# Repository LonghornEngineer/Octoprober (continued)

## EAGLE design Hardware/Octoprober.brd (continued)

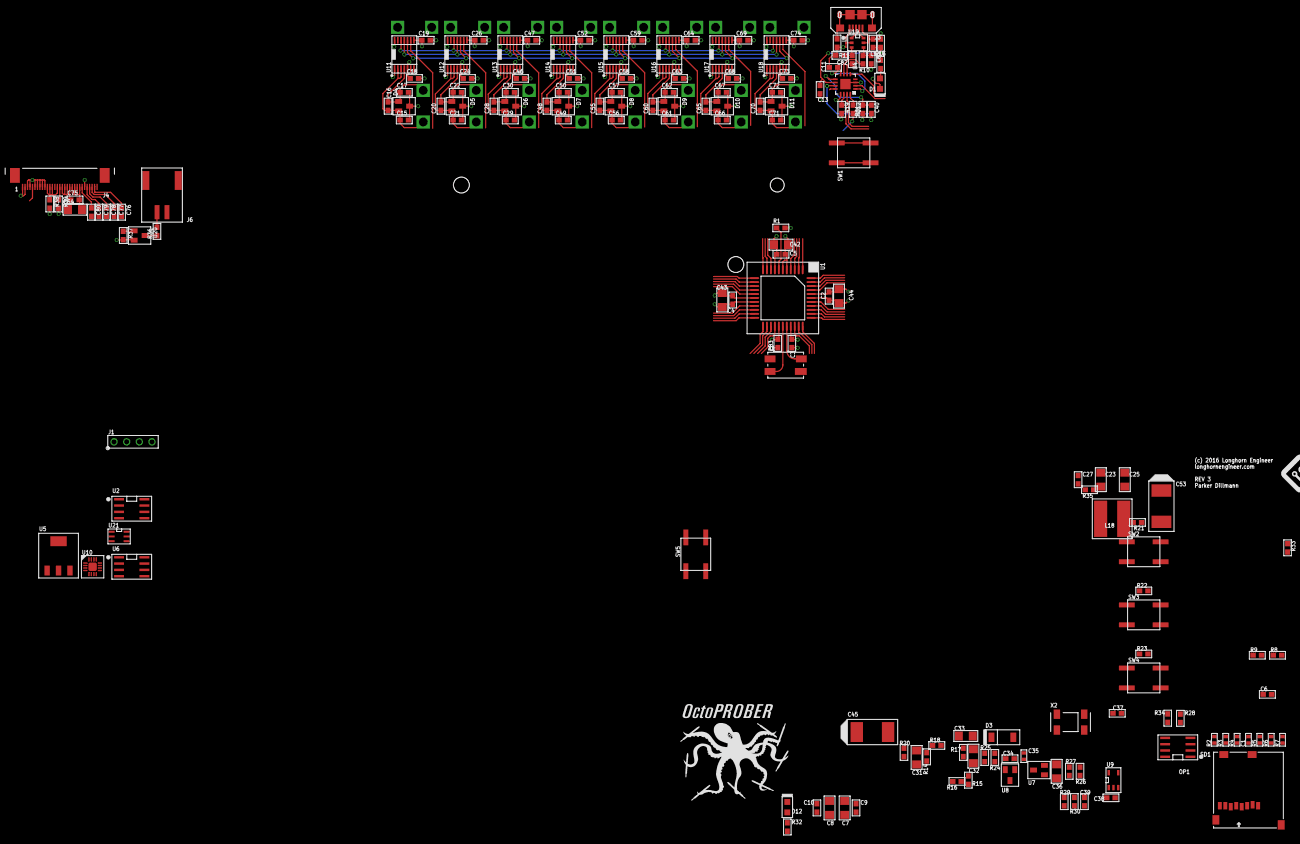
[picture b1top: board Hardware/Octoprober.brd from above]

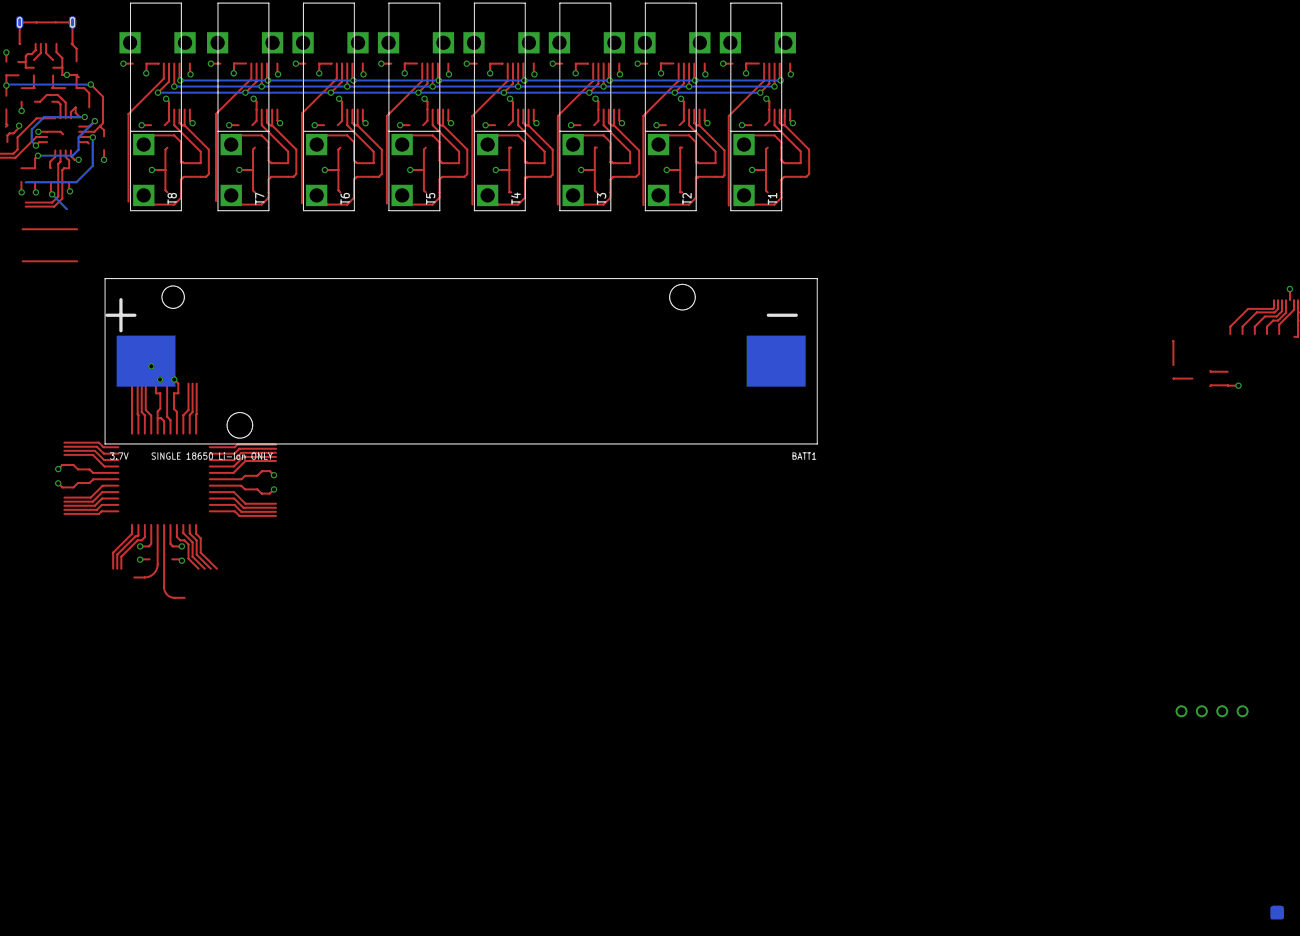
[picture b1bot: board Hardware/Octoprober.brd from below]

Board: 4 copper layers, 179 parts (9 on the bottom side), 104 nets.

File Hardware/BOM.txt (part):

"Part";"Value";"Device";"Package";"Description";"DNAME";"REVNUM";
"BATT1";"MIKROE-1120";"PH_1X02HEADER_PTH";"HEADER_01X02_PTH";"2 pin connectors";"";"";
"C1";"0.1uF";"CAPACITOR_NON_POLAR0402";"0402";"Capacitor Non Polarized";"";"";
"C2";"0.1uF";"CAPACITOR_NON_POLAR0402";"0402";"Capacitor Non Polarized";"";"";
"C3";"0.1uF";"CAPACITOR_NON_POLAR0402";"0402";"Capacitor Non Polarized";"";"";
"C4";"0.1uF";"CAPACITOR_NON_POLAR0402";"0402";"Capacitor Non Polarized";"";"";
"C5";"0.1uF";"CAPACITOR_NON_POLAR0402";"0402";"Capacitor Non Polarized";"";"";
"C6";"0.1uF";"CAPACITOR_NON_POLAR0402";"0402";"Capacitor Non Polarized";"";"";
"C7";"10uF";"CAPACITOR_NON_POLAR1206";"1206";"Capacitor Non Polarized";"";"";
"C8";"10uF";"CAPACITOR_NON_POLAR1206";"1206";"Capacitor Non Polarized";"";"";
"C9";"0.1uF";"CAPACITOR_NON_POLAR0402";"0402";"Capacitor Non Polarized";"";"";
"C10";"0.1uF";"CAPACITOR_NON_POLAR0402";"0402";"Capacitor Non Polarized";"";"";
"C11";"0.1uF";"CAPACITOR_NON_POLAR0402";"0402";"Capacitor Non Polarized";"";"";
"C12";"0.1uF";"CAPACITOR_NON_POLAR0402";"0402";"Capacitor Non Polarized";"";"";
"C13";"0.1uF";"CAPACITOR_NON_POLAR0402";"0402";"Capacitor Non Polarized";"";"";
"C14";"0.1uF";"CAPACITOR_NON_POLAR0402";"0402";"Capacitor Non Polarized";"";"";
"C15";"0.1uF";"CAPACITOR_NON_POLAR0402";"0402";"Capacitor Non Polarized";"";"";
"C16";"0.01uF";"CAPACITOR_NON_POLAR0402";"0402";"Capacitor Non Polarized";"";"";
"C17";"10uF";"CAPACITOR_NON_POLAR0402";"0402";"Capacitor Non Polarized";"";"";
"C18";"0.01uF";"CAPACITOR_NON_POLAR0402";"0402";"Capacitor Non Polarized";"";"";
"C19";"10uF";"CAPACITOR_NON_POLAR0402";"0402";"Capacitor Non Polarized";"";"";
"C20";"0.01uF";"CAPACITOR_NON_POLAR0402";"0402";"Capacitor Non Polarized";"";"";
"C21";"0.1uF";"CAPACITOR_NON_POLAR0402";"0402";"Capacitor Non Polarized";"";"";
"C22";"0.01uF";"CAPACITOR_NON_POLAR0402";"0402";"Capacitor Non Polarized";"";"";
"C23";"10uF";"CAPACITOR_NON_POLAR0402";"0402";"Capacitor Non Polarized";"";"";
"C24";"0.01uF";"CAPACITOR_NON_POLAR0402";"0402";"Capacitor Non Polarized";"";"";
"C25";"10uF";"CAPACITOR_NON_POLAR0402";"0402";"Capacitor Non Polarized";"";"";
"C26";"0.01uF";"CAPACITOR_NON_POLAR0402";"0402";"Capacitor Non Polarized";"";"";
"C27";"1uF";"CAPACITOR_NON_POLAR0402";"0402";"Capacitor Non Polarized";"";"";
"C28";"0.01uF";"CAPACITOR_NON_POLAR0402";"0402";"Capacitor Non Polarized";"";"";
"C29";"0.1uF";"CAPACITOR_NON_POLAR0402";"0402";"Capacitor Non Polarized";"";"";
"C30";"0.01uF";"CAPACITOR_NON_POLAR0402";"0402";"Capacitor Non Polarized";"";"";
"C31";"10uF";"CAPACITOR_NON_POLAR1206";"1206";"Capacitor Non Polarized";"";"";
"C32";"10uF";"CAPACITOR_NON_POLAR1206";"1206";"Capacitor Non Polarized";"";"";
"C33";"10uF";"CAPACITOR_NON_POLAR1206";"1206";"Capacitor Non Polarized";"";"";
"C34";"0.1uF";"CAPACITOR_NON_POLAR0402";"0402";"Capacitor Non Polarized";"";"";
"C35";"0.1uF";"CAPACITOR_NON_POLAR0402";"0402";"Capacitor Non Polarized";"";"";
"C36";"10uF";"CAPACITOR_NON_POLAR1206";"1206";"Capacitor Non Polarized";"";"";
"C37";"0.1uF";"CAPACITOR_NON_POLAR0402";"0402";"Capacitor Non Polarized";"";"";
"C38";"0.1uF";"CAPACITOR_NON_POLAR0402";"0402";"Capacitor Non Polarized";"";"";
"C39";"0.1uF";"CAPACITOR_NON_POLAR0402";"0402";"Capacitor Non Polarized";"";"";
"C40";"0.1uF";"CAPACITOR_NON_POLAR0402";"0402";"Capacitor Non Polarized";"";"";
"C41";"10uF";"CAPACITOR_NON_POLAR0402";"0402";"Capacitor Non Polarized";"";"";
"C42";"10uF";"CAPACITOR_NON_POLAR0402";"0402";"Capacitor Non Polarized";"";"";
"C43";"10uF";"CAPACITOR_NON_POLAR0402";"0402";"Capacitor Non Polarized";"";"";
"C44";"10uF";"CAPACITOR_NON_POLAR0402";"0402";"Capacitor Non Polarized";"";"";
"C45";"470uF";"CAPACITOR_POLARIZEDCASE_D";"CASE_D";"Polarized capacitors";"";"";
"C46";"0.1uF";"CAPACITOR_NON_POLAR0402";"0402";"Capacitor Non Polarized";"";"";
"C47";"0.1uF";"CAPACITOR_NON_POLAR0402";"0402";"Capacitor Non Polarized";"";"";
"C48";"0.1uF";"CAPACITOR_NON_POLAR0402";"0402";"Capacitor Non Polarized";"";"";
"C49";"0.1uF";"CAPACITOR_NON_POLAR0402";"0402";"Capacitor Non Polarized";"";"";
"C50";"0.1uF";"CAPACITOR_NON_POLAR0402";"0402";"Capacitor Non Polarized";"";"";
"C51";"0.1uF";"CAPACITOR_NON_POLAR0402";"0402";"Capacitor Non Polarized";"";"";
"C52";"0.1uF";"CAPACITOR_NON_POLAR0402";"0402";"Capacitor Non Polarized";"";"";
"C53";"470uF";"CAPACITOR_POLARIZEDCASE_D";"CASE_D";"Polarized capacitors";"";"";
"C54";"1uF";"CAPACITOR_NON_POLAR0402";"0402";"Capacitor Non Polarized";"";"";
"D1";"598-8070-107F";"LED_SINGLE0402";"LED_0402";"";"";"";
"D2";"598-8070-107F";"LED_SINGLE0402";"LED_0402";"";"";"";
"D3";"PMEG6030EP,115";"DIODESOD-128";"SOD-128";"Diode - Single";"";"";
"D4";"NUP2105LT1G";"TVS_DIODE_DUALSOT-23";"SOT-23";"";"";"";
"D5";"NUP2105LT1G";"TVS_DIODE_DUALSOT-23";"SOT-23";"";"";"";
"D6";"NUP2105LT1G";"TVS_DIODE_DUALSOT-23";"SOT-23";"";"";"";
"D7";"NUP2105LT1G";"TVS_DIODE_DUALSOT-23";"SOT-23";"";"";"";
"D8";"NUP2105LT1G";"TVS_DIODE_DUALSOT-23";"SOT-23";"";"";"";
"D9";"NUP2105LT1G";"TVS_DIODE_DUALSOT-23";"SOT-23";"";"";"";
"D10";"NUP2105LT1G";"TVS_DIODE_DUALSOT-23";"SOT-23";"";"";"";
"D11";"NUP2105LT1G";"TVS_DIODE_DUALSOT-23";"SOT-23";"";"";"";
"D12";"598-8070-107F";"LED_SINGLE0402";"LED_0402";"";"";"";
"FU";"";"PH_1X09PTH";"HEADER_01X09_PTH";"";"";"";
"J1";"10118193-0001LF";"USB10118193-0001LF";"10118193-0001LF";"";"";"";
"J2";"";"PH_1X04HEADER_PTH";"HEADER_01X04_PTH";"4 Pin Connectors";"";"";
"L1";"MI0603K300R-10";"RESISTOR0603";"0603";"Resistors";"";"";
"L2";"BK1005HM471-T";"INDUCTOR0402";"0402";"Inductors";"";"";
"L3";"BK1005HM471-T";"INDUCTOR0402";"0402";"Inductors";"";"";
"L4";"BK1005HM471-T";"INDUCTOR0402";"0402";"Inductors";"";"";
"L5";"BK1005HM471-T";"INDUCTOR0402";"0402";"Inductors";"";"";
"L6";"BK1005HM471-T";"INDUCTOR0402";"0402";"Inductors";"";"";
"L7";"BK1005HM471-T";"INDUCTOR0402";"0402";"Inductors";"";"";
"L8";"BK1005HM471-T";"INDUCTOR0402";"0402";"Inductors";"";"";
"L9";"BK1005HM471-T";"INDUCTOR0402";"0402";"Inductors";"";"";
"L10";"BK1005HM471-T";"INDUCTOR0402";"0402";"Inductors";"";"";
"L11";"BK1005HM471-T";"INDUCTOR0402";"0402";"Inductors";"";"";
"L12";"BK1005HM471-T";"INDUCTOR0402";"0402";"Inductors";"";"";
"L13";"BK1005HM471-T";"INDUCTOR0402";"0402";"Inductors";"";"";
"L14";"BK1005HM471-T";"INDUCTOR0402";"0402";"Inductors";"";"";
"L15";"BK1005HM471-T";"INDUCTOR0402";"0402";"Inductors";"";"";
"L16";"BK1005HM471-T";"INDUCTOR0402";"0402";"Inductors";"";"";
"L17";"BK1005HM471-T";"INDUCTOR0402";"0402";"Inductors";"";"";
"L18";"LK1608100K-T";"INDUCTOR0603";"0603";"Inductors";"";"";
"LCD1";"";"HD44780_LCD1602_COUNTERSINK";"CHAR_DISPLAY_1602_COUNTERSINK";"";"";"";
"OP1";"ACPL-227";"ACPL-227SOIC-8";"SOIC-8";"";"";"";
"R1";"10K";"RESISTOR0402";"0402";"Resistors";"";"";
"R2";"10K";"RESISTOR0402";"0402";"Resistors";"";"";
"R3";"10K";"RESISTOR0402";"0402";"Resistors";"";"";
"R4";"10K";"RESISTOR0402";"0402";"Resistors";"";"";
"R5";"10K";"RESISTOR0402";"0402";"Resistors";"";"";
"R6";"10K";"RESISTOR0402";"0402";"Resistors";"";"";
"R7";"10K";"RESISTOR0402";"0402";"Resistors";"";"";
"R8";"10K";"RESISTOR0402";"0402";"Resistors";"";"";
"R9";"10K";"RESISTOR0402";"0402";"Resistors";"";"";
"R10";"22";"RESISTOR0402";"0402";"Resistors";"";"";
"R11";"22";"RESISTOR0402";"0402";"Resistors";"";"";
"R12";"330";"RESISTOR0402";"0402";"Resistors";"";"";
"R13";"330";"RESISTOR0402";"0402";"Resistors";"";"";
"R14";"10K";"RESISTOR0402";"0402";"Resistors";"";"";
"R15";"10K";"RESISTOR0402";"0402";"Resistors";"";"";
"R16";"10K";"RESISTOR0402";"0402";"Resistors";"";"";
"R17";"1.18K";"RESISTOR0402";"0402";"Resistors";"";"";
"R18";"1.13K";"RESISTOR0402";"0402";"Resistors";"";"";
"R19";"10K";"RESISTOR0402";"0402";"Resistors";"";"";
"R20";"10K";"RESISTOR0402";"0402";"Resistors";"";"";
"R21";"10K";"RESISTOR0402";"0402";"Resistors";"";"";
"R22";"10K";"RESISTOR0402";"0402";"Resistors";"";"";
"R23";"10K";"RESISTOR0402";"0402";"Resistors";"";"";
"R24";"100K";"RESISTOR0402";"0402";"Resistors";"";"";
"R25";"10K";"RESISTOR0402";"0402";"Resistors";"";"";
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
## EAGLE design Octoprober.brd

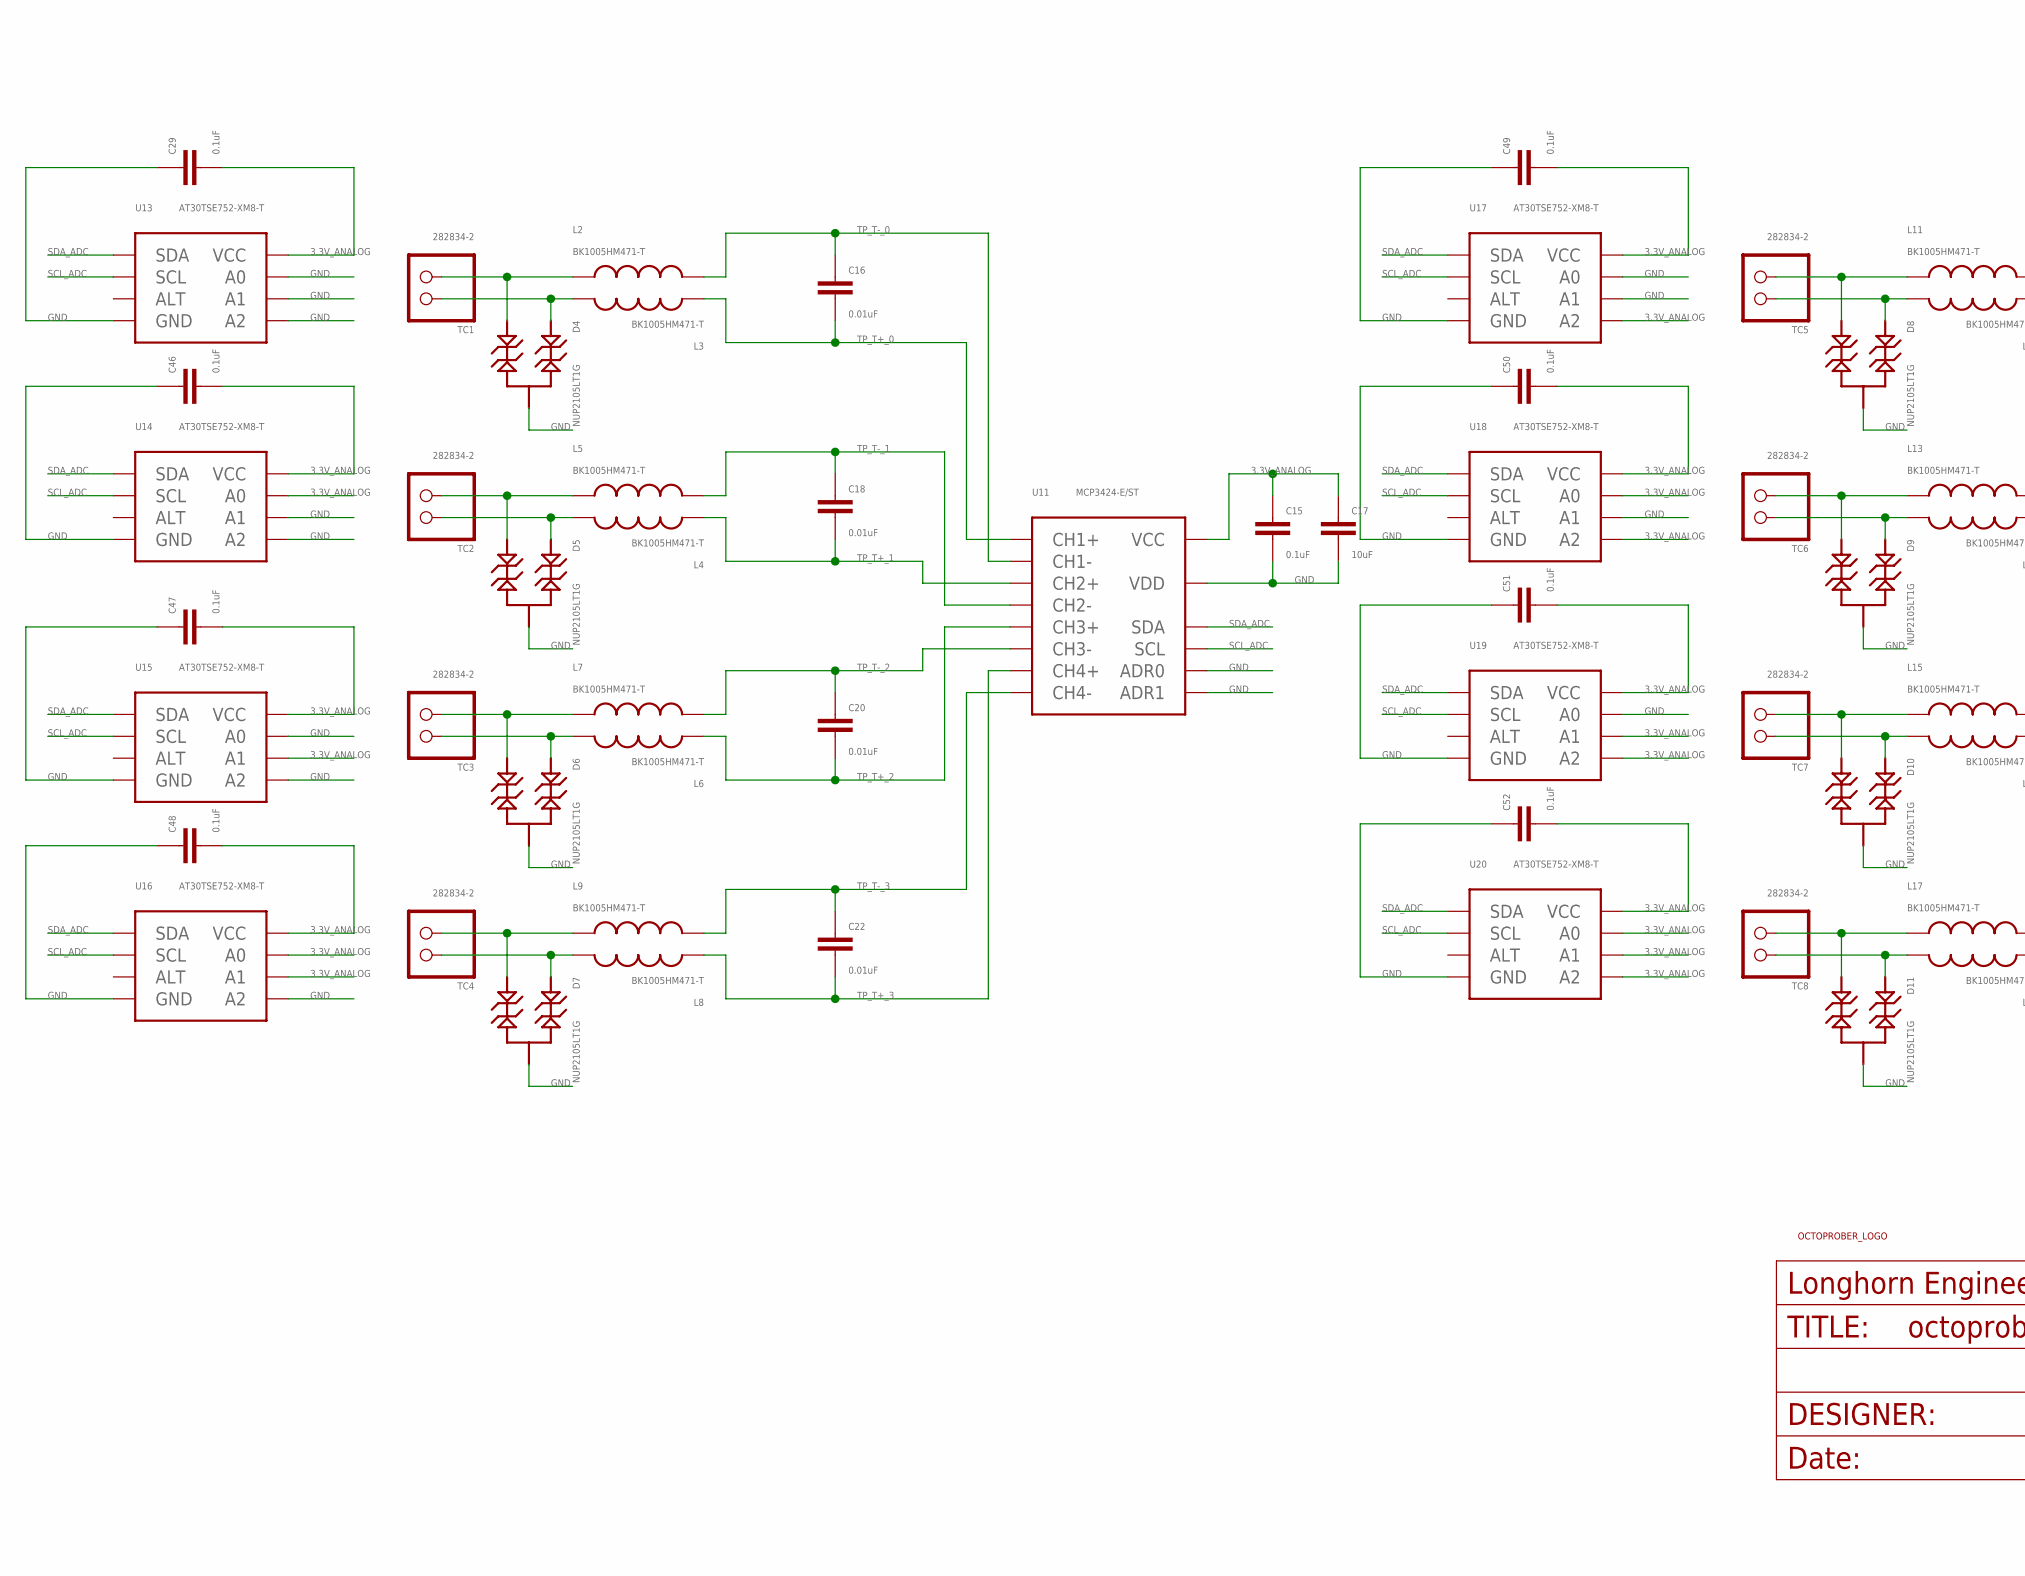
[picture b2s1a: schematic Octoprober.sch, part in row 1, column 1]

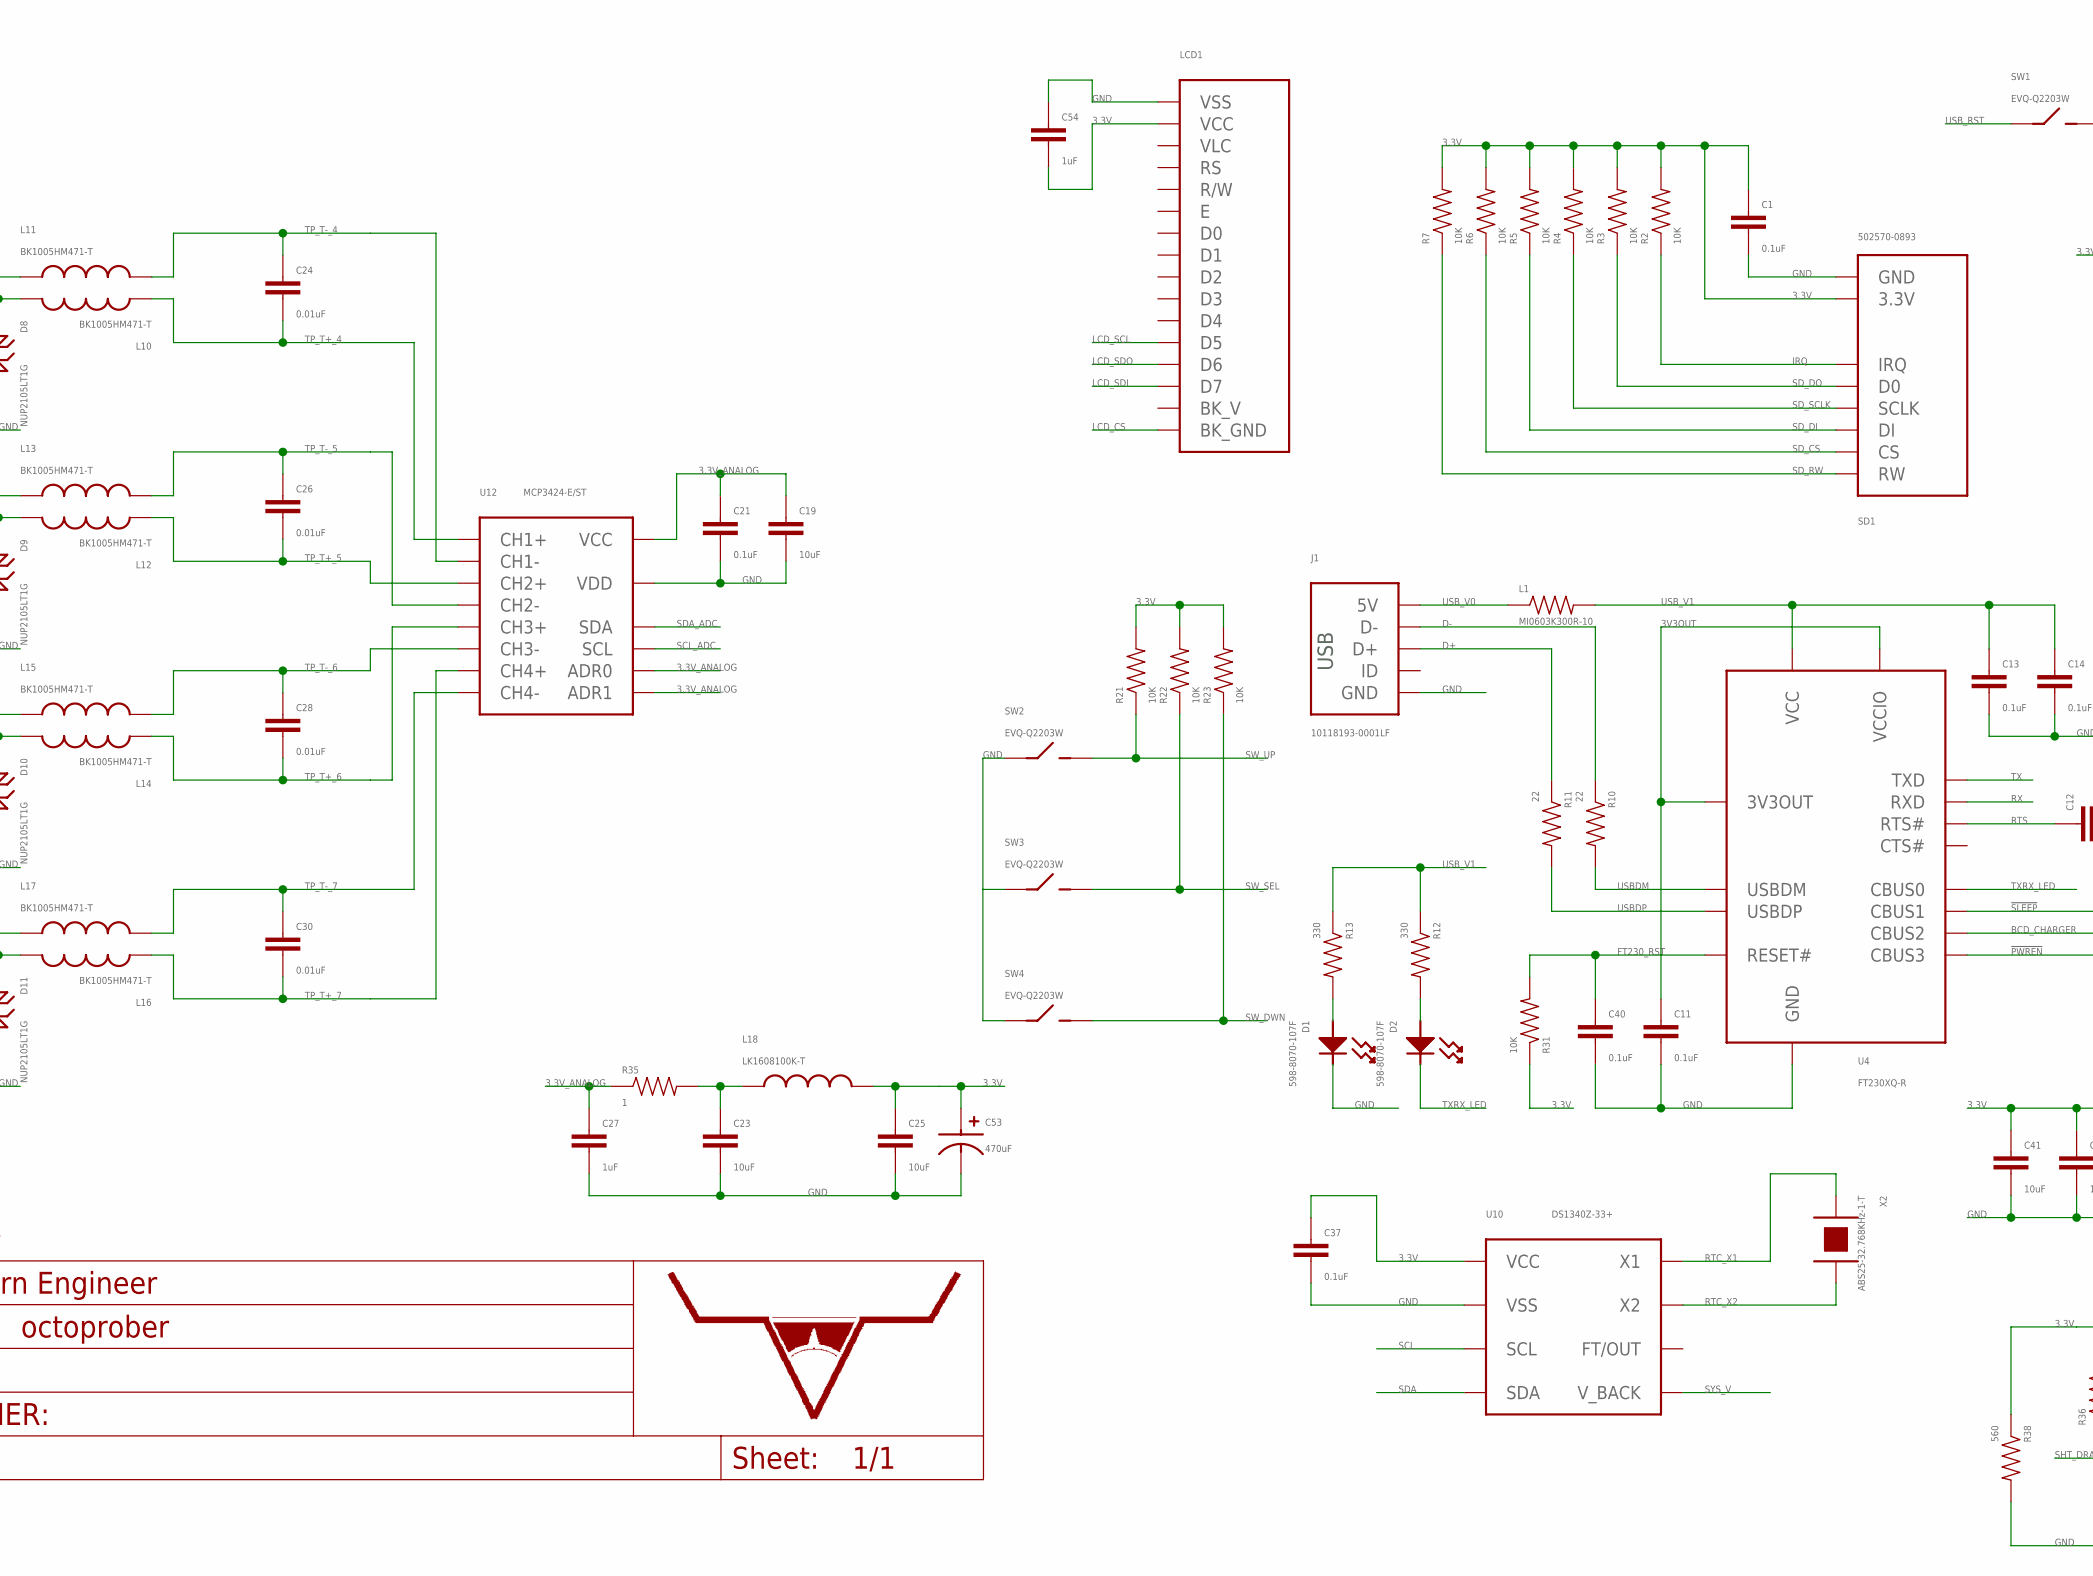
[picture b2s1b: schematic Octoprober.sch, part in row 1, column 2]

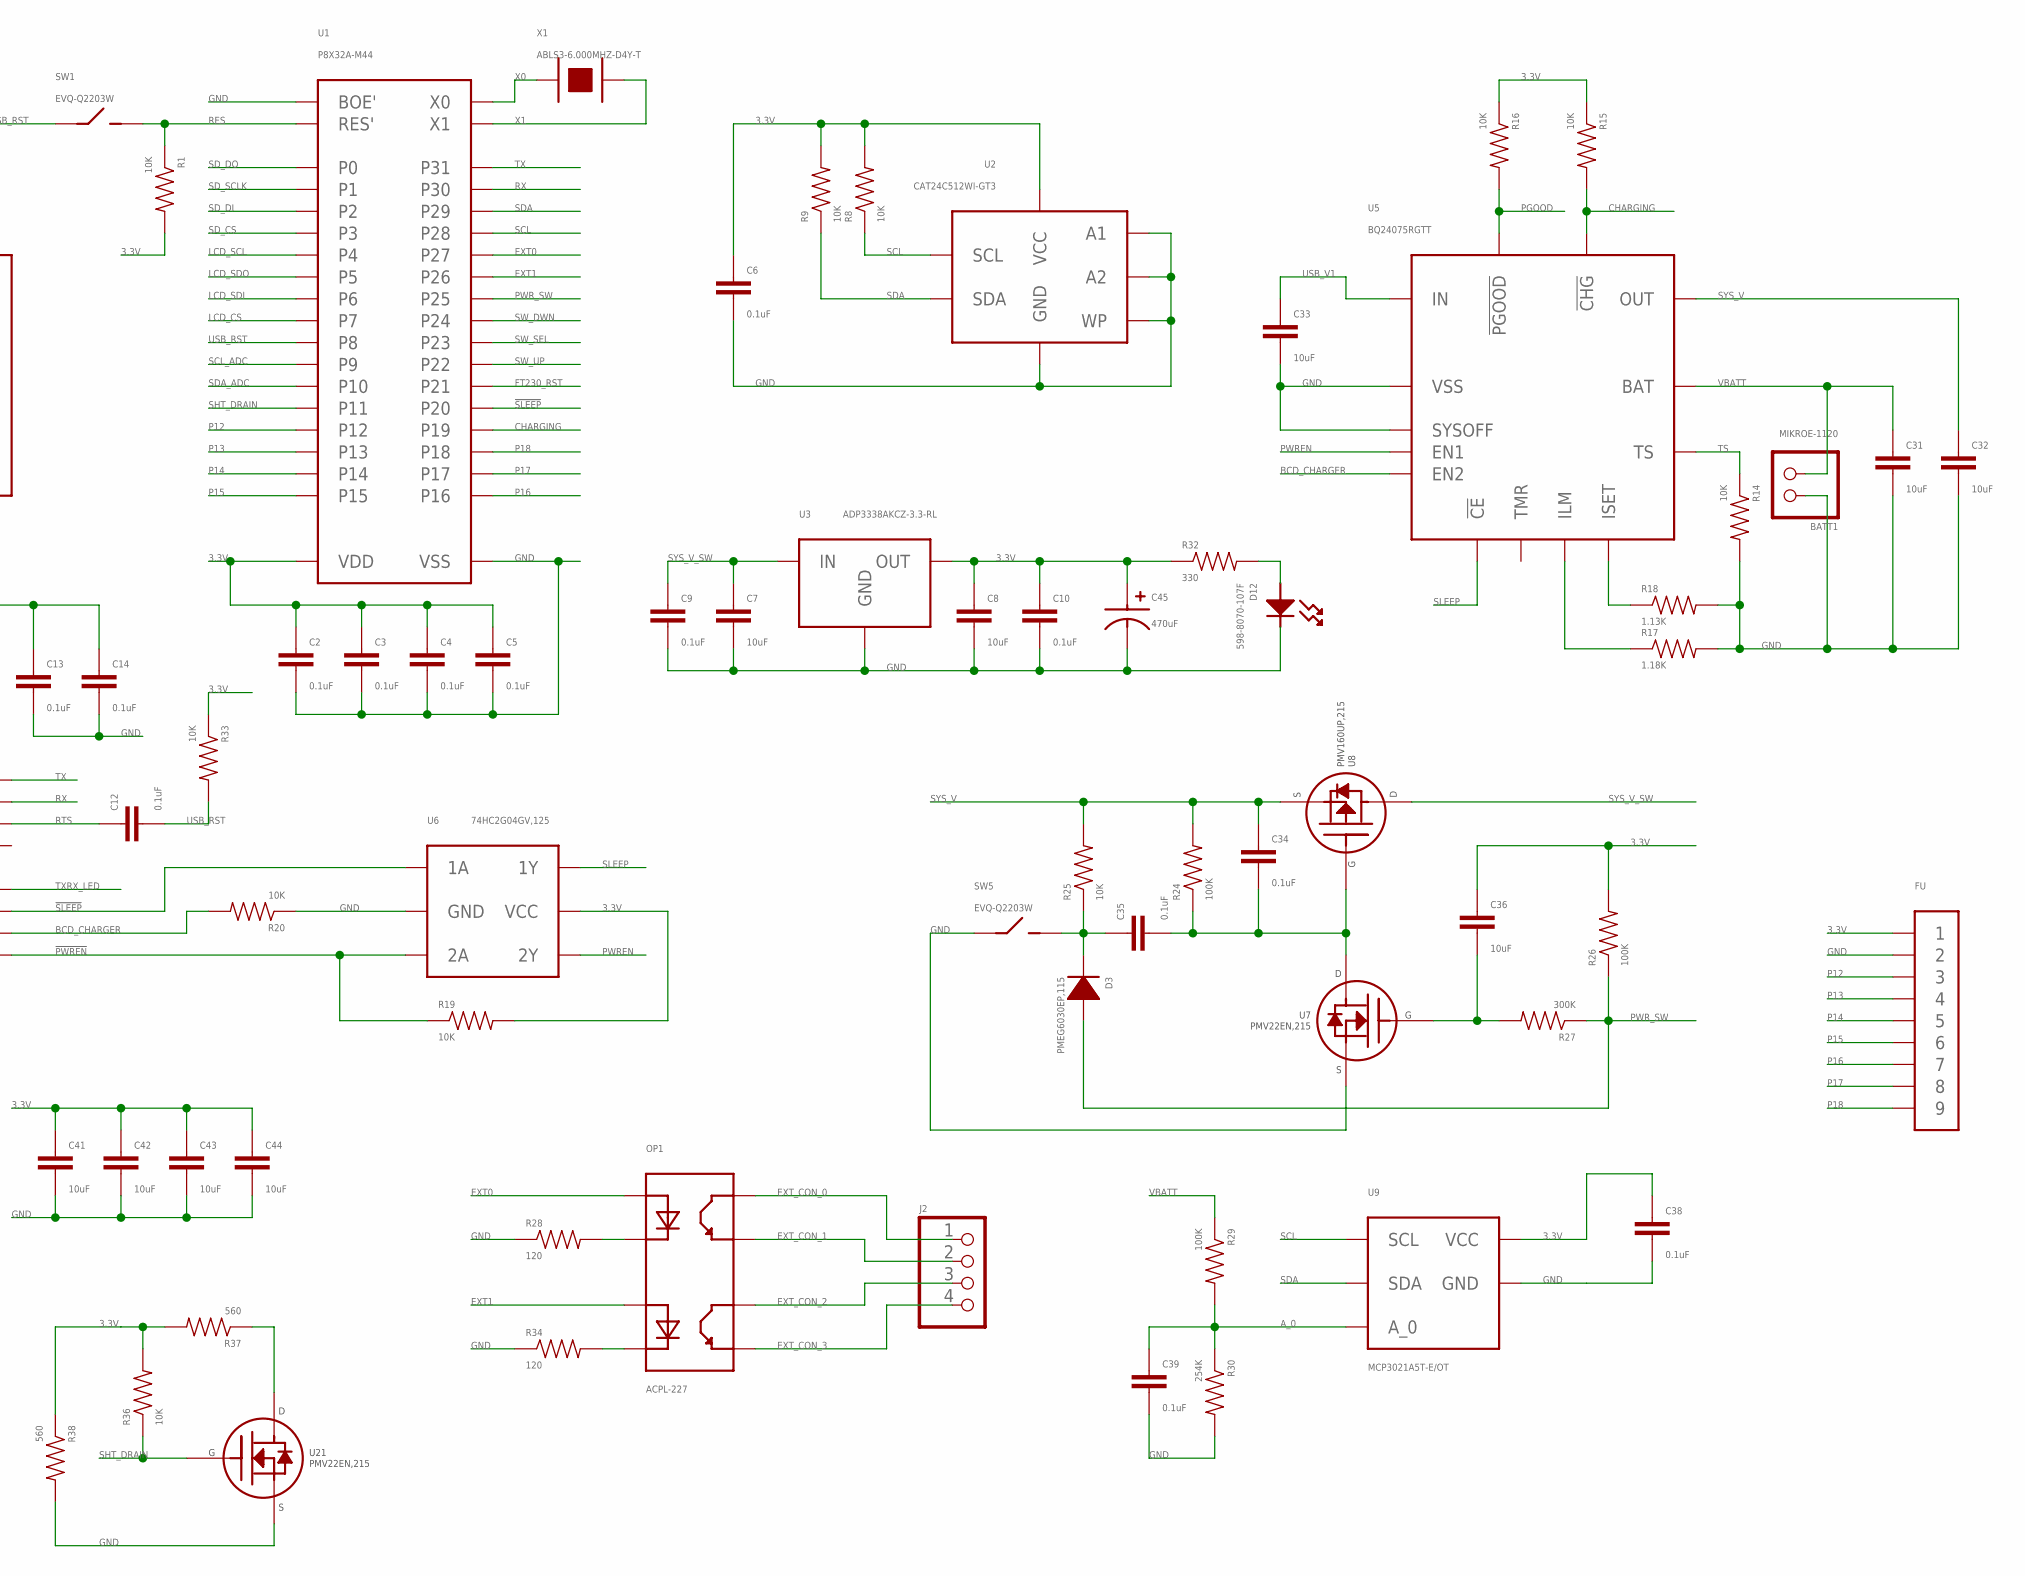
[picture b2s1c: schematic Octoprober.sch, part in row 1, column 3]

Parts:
BATT1: MIKROE-1120; HEADER_01X02_PTH
C1, C2, C3, C4, C5, C6, C9, C10, C11, C12, C13, C14, C15, C21, C29, C34, C35, C37, C38, C39, C40, C46, C47, C48, C49, C50, C51, C52: 0.1uF; 0402
C7, C8, C31, C32, C33, C36: 10uF; 1206
C16, C18, C20, C22, C24, C26, C28, C30: 0.01uF; 0402
C17, C19, C23, C25, C41, C42, C43, C44: 10uF; 0402
C27, C54: 1uF; 0402
C45, C53: 470uF; CASE_D
D1, D2, D12: 598-8070-107F; LED_0402
D3: PMEG6030EP,115; SOD-128
D4, D5, D6, D7, D8, D9, D10, D11: NUP2105LT1G; SOT-23
FU: PH_1X09PTH; HEADER_01X09_PTH
J1: 10118193-0001LF
J2: PH_1X04HEADER_PTH; HEADER_01X04_PTH
L1: MI0603K300R-10; 0603
L2, L3, L4, L5, L6, L7, L8, L9, L10, L11, L12, L13, L14, L15, L16, L17: BK1005HM471-T; 0402
L18: LK1608100K-T; 0603
LCD1: HD44780_LCD1602_COUNTERSINK; CHAR_DISPLAY_1602_COUNTERSINK
OP1: ACPL-227; SOIC-8
R1, R2, R3, R4, R5, R6, R7, R8, R9, R14, R15, R16, R19, R20, R21, R22, R23, R25, R31, R33, R36: 10K; 0402
R10, R11: 22; 0402
R12, R13, R32: 330; 0402
R17: 1.18K; 0402
R18: 1.13K; 0402
R24, R26, R29: 100K; 0402
R27: 300K; 0402
R28, R34: 120; 0402
R30: 254K; 0402
R35: 1; 0402
R37, R38: 560; 0402
SD1: 502570-0893
SW1, SW2, SW3, SW4, SW5: EVQ-Q2203W
TC1, TC2, TC3, TC4, TC5, TC6, TC7, TC8: 282834-2; HEADER_01X02_PTH_SCREWTERM
U1: P8X32A-M44; QFN-44
U2: CAT24C512WI-GT3; SOIC-8_W
U3: ADP3338AKCZ-3.3-RL; SOT-223
U4: FT230XQ-R; QFN-16
U5: BQ24075RGTT; QFN-16_BOT_PAD
U6: 74HC2G04GV,125; TTSOP-6
U7, U21: PMV22EN,215; SOT-23
U8: PMV160UP,215; SOT-23
U9: MCP3021A5T-E/OT; SOT-23A
U10: DS1340Z-33+; SOIC-8
U11, U12: MCP3424-E/ST; TTSOP-14
U13, U14, U15, U16, U17, U18, U19, U20: AT30TSE752-XM8-T; MSOP-8
U$1: LHE_FRAME
U$2: OCTOPROBER_LOGONORMAL; OCTOPROBER_LOGO
X1: ABLS3-6.000MHZ-D4Y-T; HC-49/US_SM
X2: ABS25-32.768KHz-1-T; 8MM_X_3.8MM

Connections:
3.3V: C1.1, C2.1, C3.1, C4.1, C5.1, C6.1, C8.1, C10.1, C25.1, C36.1, C37.1, C38.1, C41.1, C42.1, C43.1, C44.1, C45.P (POS), C53.P (POS), C54.2, FU.1, L18.2, LCD1.2 (VCC), R1.2, R2.2, R3.2, R4.2, R5.2, R6.2, R7.2, R8.2, R9.2, R15.1, R16.1, R19.2, R21.2, R22.2, R23.2, R26.2, R31.1, R32.1, R33.1, R36.2, R37.2, R38.1, SD1.5 (3.3V), U1.8 (VDD), U1.18 (VDD), U1.30 (VDD), U1.40 (VDD), U2.8 (VCC), U3.COM1 (OUT), U3.COM2 (OUT), U6.5 (VCC), U9.1 (VCC), U10.8 (VCC)
3.3V_ANALOG: C15.1, C17.1, C19.1, C21.1, C27.1, C29.2, C46.2, C47.2, C48.2, C49.2, C50.2, C51.2, C52.2, R35.1, U11.5 (VCC), U12.5 (VCC), U12.9 (ADR0), U12.10 (ADR1), U13.P$8 (VCC), U14.P$7 (A0), U14.P$8 (VCC), U15.P$6 (A1), U15.P$8 (VCC), U16.P$6 (A1), U16.P$7 (A0), U16.P$8 (VCC), U17.P$5 (A2), U17.P$8 (VCC), U18.P$5 (A2), U18.P$7 (A0), U18.P$8 (VCC), U19.P$5 (A2), U19.P$6 (A1), U19.P$8 (VCC), U20.P$5 (A2), U20.P$6 (A1), U20.P$7 (A0), U20.P$8 (VCC)
3V3OUT: C11.1, U4.1 (VCCIO), U4.8 (3V3OUT)
!PWREN: R19.1, U4.14 (CBUS3), U6.3 (2A)
!SLEEP: U1.23 (P20), U4.11 (CBUS1), U6.1 (1A)
A_0: C39.1, R29.2, R30.1, U9.3 (A_0)
BCD_CHARGER: R20.2, U4.5 (CBUS2), U5.5 (EN2)
CHARGING: R15.2, U1.22 (P19), U5.9 (!CHG)
D+: J1.3 (D+), R11.1
D-: J1.2 (D-), R10.1
EXT0: OP1.1, U1.34 (P27)
EXT1: OP1.3, U1.33 (P26)
EXT_CON_0: J2.1, OP1.8
EXT_CON_1: J2.2, OP1.7
EXT_CON_2: J2.3, OP1.6
EXT_CON_3: J2.4, OP1.5
FT230_RST: C40.1, R31.2, U1.24 (P21), U4.9 (RESET#)
GND: BATT1.1, C1.2, C2.2, C3.2, C4.2, C5.2, C6.2, C7.2, C8.2, C9.2, C10.2, C11.2, C13.2, C14.2, C15.2, C17.2, C19.2, C21.2, C23.2, C25.2, C27.2, C29.1, C31.2, C32.2, C33.2, C37.2, C38.2, C39.2, C40.2, C41.2, C42.2, C43.2, C44.2, C45.N (NEG), C46.1, C47.1, C48.1, C49.1, C50.1, C51.1, C52.1, C53.N (NEG), C54.1, D1.CATHODE, D4.3, D5.3, D6.3, D7.3, D8.3, D9.3, D10.3, D11.3, D12.CATHODE, FU.2, J1.5 (GND), J1.S1 (GND), J1.S2 (GND), J1.S3 (GND), J1.S4 (GND), LCD1.1 (VSS), R14.2, R17.2, R18.2, R20.1, R28.1, R30.2, R34.1, R38.2, SD1.3 (GND), SD1.SHIELD0 (GND), SD1.SHIELD1 (GND), SD1.SHIELD2 (GND), SD1.SHIELD3 (GND), SW2.1 (A), SW2.2 (A), SW3.1 (A), SW3.2 (A), SW4.1 (A), SW4.2 (A), SW5.1 (A), SW5.2 (A), U1.5 (VSS), U1.6 (BOE'), U1.17 (VSS), U1.27 (VSS), U1.39 (VSS), U2.2 (A1), U2.3 (A2), U2.4 (GND), U2.7 (WP), U3.IN (GND), U4.3 (GND), U4.13 (GND), U4.PAD (GND), U5.8 (VSS), U5.15 (SYSOFF), U5.PAD0 (VSS), U5.PAD1 (VSS), U6.2 (GND), U7.2 (SOURCE), U9.2 (GND), U10.4 (VSS), U11.6 (VDD), U11.9 (ADR0), U11.10 (ADR1), U12.6 (VDD), U13.P$4 (GND), U13.P$5 (A2), U13.P$6 (A1), U13.P$7 (A0), U14.P$4 (GND), U14.P$5 (A2), U14.P$6 (A1), U15.P$4 (GND), U15.P$5 (A2), U15.P$7 (A0), U16.P$4 (GND), U16.P$5 (A2), U17.P$4 (GND), U17.P$6 (A1), U17.P$7 (A0), U18.P$4 (GND), U18.P$6 (A1), U19.P$4 (GND), U19.P$7 (A0), U20.P$4 (GND), U21.2 (SOURCE)
ILM: R17.1, U5.12 (ILM)
IRQ: R2.1, SD1.1 (IRQ)
ISET: R18.1, U5.16 (ISET)
LCD_CS: LCD1.16 (BK_GND), U1.4 (P7)
LCD_SCL: LCD1.12 (D5), U1.1 (P4)
LCD_SDI: LCD1.14 (D7), U1.3 (P6)
LCD_SDO: LCD1.13 (D6), U1.2 (P5)
unnamed: D2.ANODE, R12.2
unnamed: D4.2, L2.1, TC1.2
unnamed: D1.ANODE, R13.2
unnamed: C35.1, D3.CATHODE, R25.1, SW5.3 (B), SW5.4 (B)
unnamed: C36.2, R27.2, U7.1 (GATE)
unnamed: OP1.2, R28.2
unnamed: D4.1, L3.2, TC1.1
unnamed: D5.2, L5.1, TC2.2
unnamed: D5.1, L4.2, TC2.1
unnamed: D6.2, L7.1, TC3.2
unnamed: D6.1, L6.2, TC3.1
unnamed: D7.2, L9.1, TC4.2
unnamed: D7.1, L8.2, TC4.1
unnamed: D11.2, L17.1, TC8.2
unnamed: D11.1, L16.2, TC8.1
unnamed: D10.2, L15.1, TC7.2
unnamed: D10.1, L14.2, TC7.1
unnamed: D9.2, L13.1, TC6.2
unnamed: D9.1, L12.2, TC6.1
unnamed: D8.2, L11.1, TC5.2
unnamed: D8.1, L10.2, TC5.1
unnamed: D12.ANODE, R32.2
unnamed: OP1.4, R34.2
unnamed: C23.1, L18.1, R35.2
unnamed: R37.1, U21.3 (DRAIN)
P12: FU.3, U1.13 (P12)
P13: FU.4, U1.14 (P13)
P14: FU.5, U1.15 (P14)
P15: FU.6, U1.16 (P15)
P16: FU.7, U1.19 (P16)
P17: FU.8, U1.20 (P17)
P18: FU.9, U1.21 (P18)
PGOOD: R16.2, U5.7 (!PGOOD)
PWREN: U5.6 (EN1), U6.4 (2Y)
PWR_SW: D3.ANODE, R26.1, R27.1, U1.32 (P25)
RES: R1.1, SW1.3 (B), SW1.4 (B), U1.7 (RES')
RTC_X1: U10.1 (X1), X2.1
RTC_X2: U10.2 (X2), X2.4
RTS: C12.1, U4.16 (RTS#)
RX: U1.37 (P30), U4.2 (RXD)
SCL: R8.1, U1.35 (P28), U2.6 (SCL), U9.5 (SCL), U10.6 (SCL)
SCL_ADC: U1.10 (P9), U11.8 (SCL), U12.8 (SCL), U13.P$2 (SCL), U14.P$2 (SCL), U15.P$2 (SCL), U16.P$2 (SCL), U17.P$2 (SCL), U18.P$2 (SCL), U19.P$2 (SCL), U20.P$2 (SCL)
SDA: R9.1, U1.36 (P29), U2.5 (SDA), U9.4 (SDA), U10.5 (SDA)
SDA_ADC: U1.11 (P10), U11.7 (SDA), U12.7 (SDA), U13.P$1 (SDA), U14.P$1 (SDA), U15.P$1 (SDA), U16.P$1 (SDA), U17.P$1 (SDA), U18.P$1 (SDA), U19.P$1 (SDA), U20.P$1 (SDA)
SD_CS: R6.1, SD1.7 (CS), U1.44 (P3)
SD_DI: R5.1, SD1.6 (DI), U1.43 (P2)
SD_DO: R3.1, SD1.2 (D0), U1.41 (P0)
SD_RW: R7.1, SD1.8 (RW)
SD_SCLK: R4.1, SD1.4 (SCLK), U1.42 (P1)
SHT_DRAIN: R36.1, U1.12 (P11), U21.1 (GATE)
SLEEP: U5.4 (!CE), U6.6 (1Y)
SW_DWN: R23.1, SW4.3 (B), SW4.4 (B), U1.31 (P24)
SW_SEL: R22.1, SW3.3 (B), SW3.4 (B), U1.26 (P23)
SW_UP: R21.1, SW2.3 (B), SW2.4 (B), U1.25 (P22)
SYS_V: C32.1, C34.1, R24.2, R25.2, U5.10 (OUT), U5.11 (OUT), U8.2 (SOURCE), U10.3 (V_BACK)
SYS_V_SW: C7.1, C9.1, U3.OUT (IN), U8.3 (DRAIN)
S_P_G: C34.2, C35.2, R24.1, U7.3 (DRAIN), U8.1 (GATE)
TP_T+_0: C16.2, L3.1, U11.1 (CH1+)
TP_T+_1: C18.2, L4.1, U11.3 (CH2+)
TP_T+_2: C20.2, L6.1, U11.11 (CH3+)
TP_T+_3: C22.2, L8.1, U11.13 (CH4+)
TP_T+_4: C24.2, L10.1, U12.1 (CH1+)
TP_T+_5: C26.2, L12.1, U12.3 (CH2+)
TP_T+_6: C28.2, L14.1, U12.11 (CH3+)
TP_T+_7: C30.2, L16.1, U12.13 (CH4+)
TP_T-_0: C16.1, L2.2, U11.2 (CH1-)
TP_T-_1: C18.1, L5.2, U11.4 (CH2-)
TP_T-_2: C20.1, L7.2, U11.12 (CH3-)
TP_T-_3: C22.1, L9.2, U11.14 (CH4-)
TP_T-_4: C24.1, L11.2, U12.2 (CH1-)
TP_T-_5: C26.1, L13.2, U12.4 (CH2-)
TP_T-_6: C28.1, L15.2, U12.12 (CH3-)
TP_T-_7: C30.1, L17.2, U12.14 (CH4-)
TS: R14.1, U5.1 (TS)
TX: U1.38 (P31), U4.15 (TXD)
TXRX_LED: D2.CATHODE, U4.12 (CBUS0)
USBDM: R10.2, U4.7 (USBDM)
USBDP: R11.2, U4.6 (USBDP)
USB_RST: C12.2, R33.2, SW1.1 (A), SW1.2 (A), U1.9 (P8)
USB_V0: J1.1 (5V), L1.1
USB_V1: C13.1, C14.1, C33.1, L1.2, R12.1, R13.1, U4.10 (VCC), U5.13 (IN)
VBATT: BATT1.2, C31.1, R29.1, U5.2 (BAT), U5.3 (BAT)
X0: U1.29 (X0), X1.P$1
X1: U1.28 (X1), X1.P$2
